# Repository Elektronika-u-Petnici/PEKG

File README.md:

# PEKG - Petnički EKG v2

Petnički EKG snima EKG signal na SD karticu i opcionalno šalje isti pomoću Bluetooth-a i android aplikacije.

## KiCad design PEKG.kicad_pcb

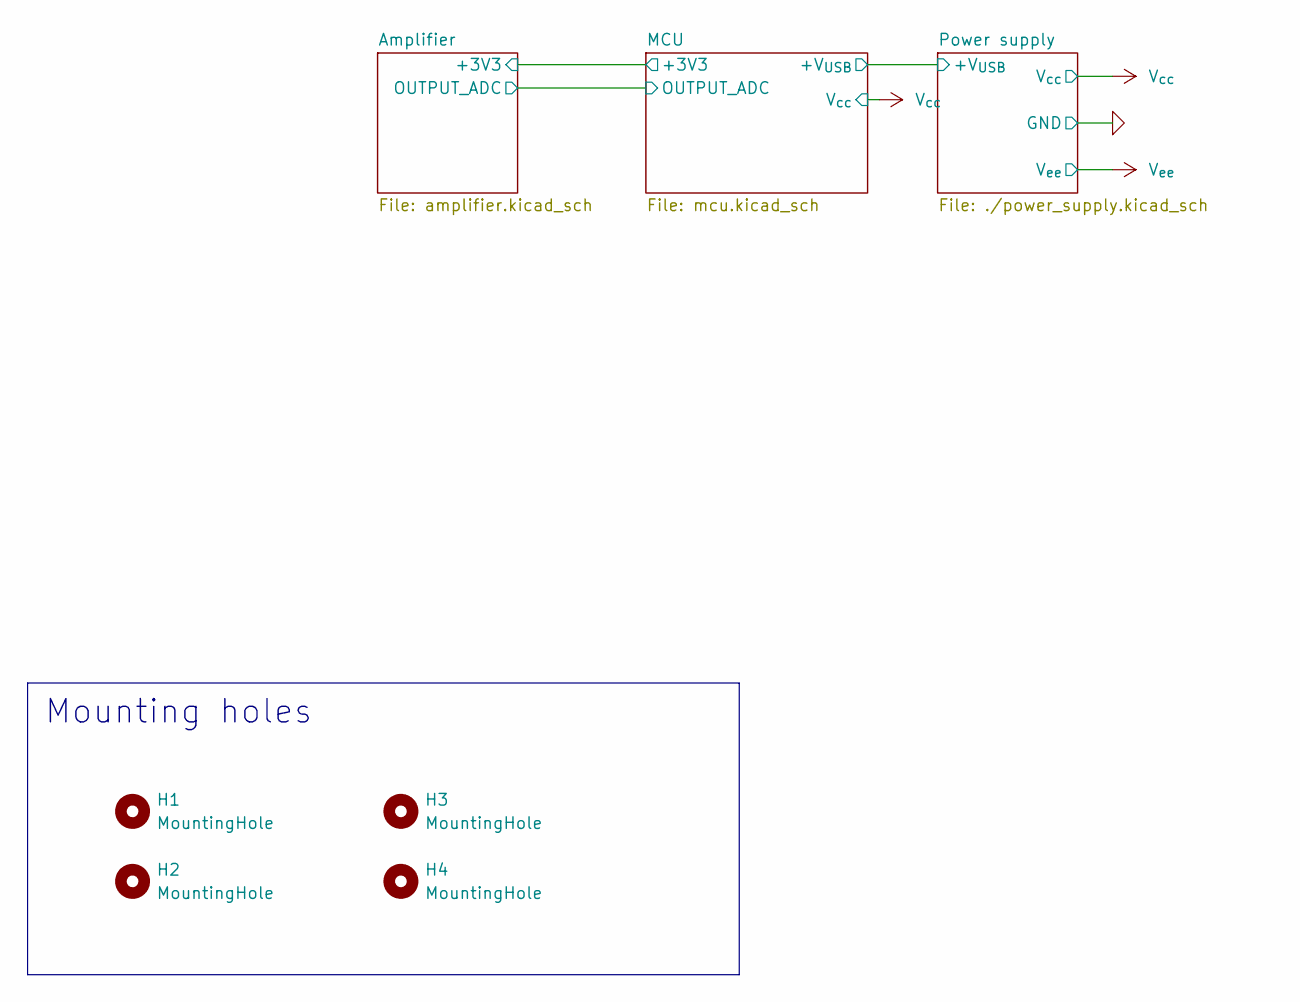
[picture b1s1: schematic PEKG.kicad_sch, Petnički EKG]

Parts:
H1, H3: MountingHole; MountingHole_3.2mm_M3_ISO14580_Pad_TopOnly
H2, H4: MountingHole; MountingHole_3.2mm_M3_ISO14580_Pad_TopBottom

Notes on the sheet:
Mounting holes

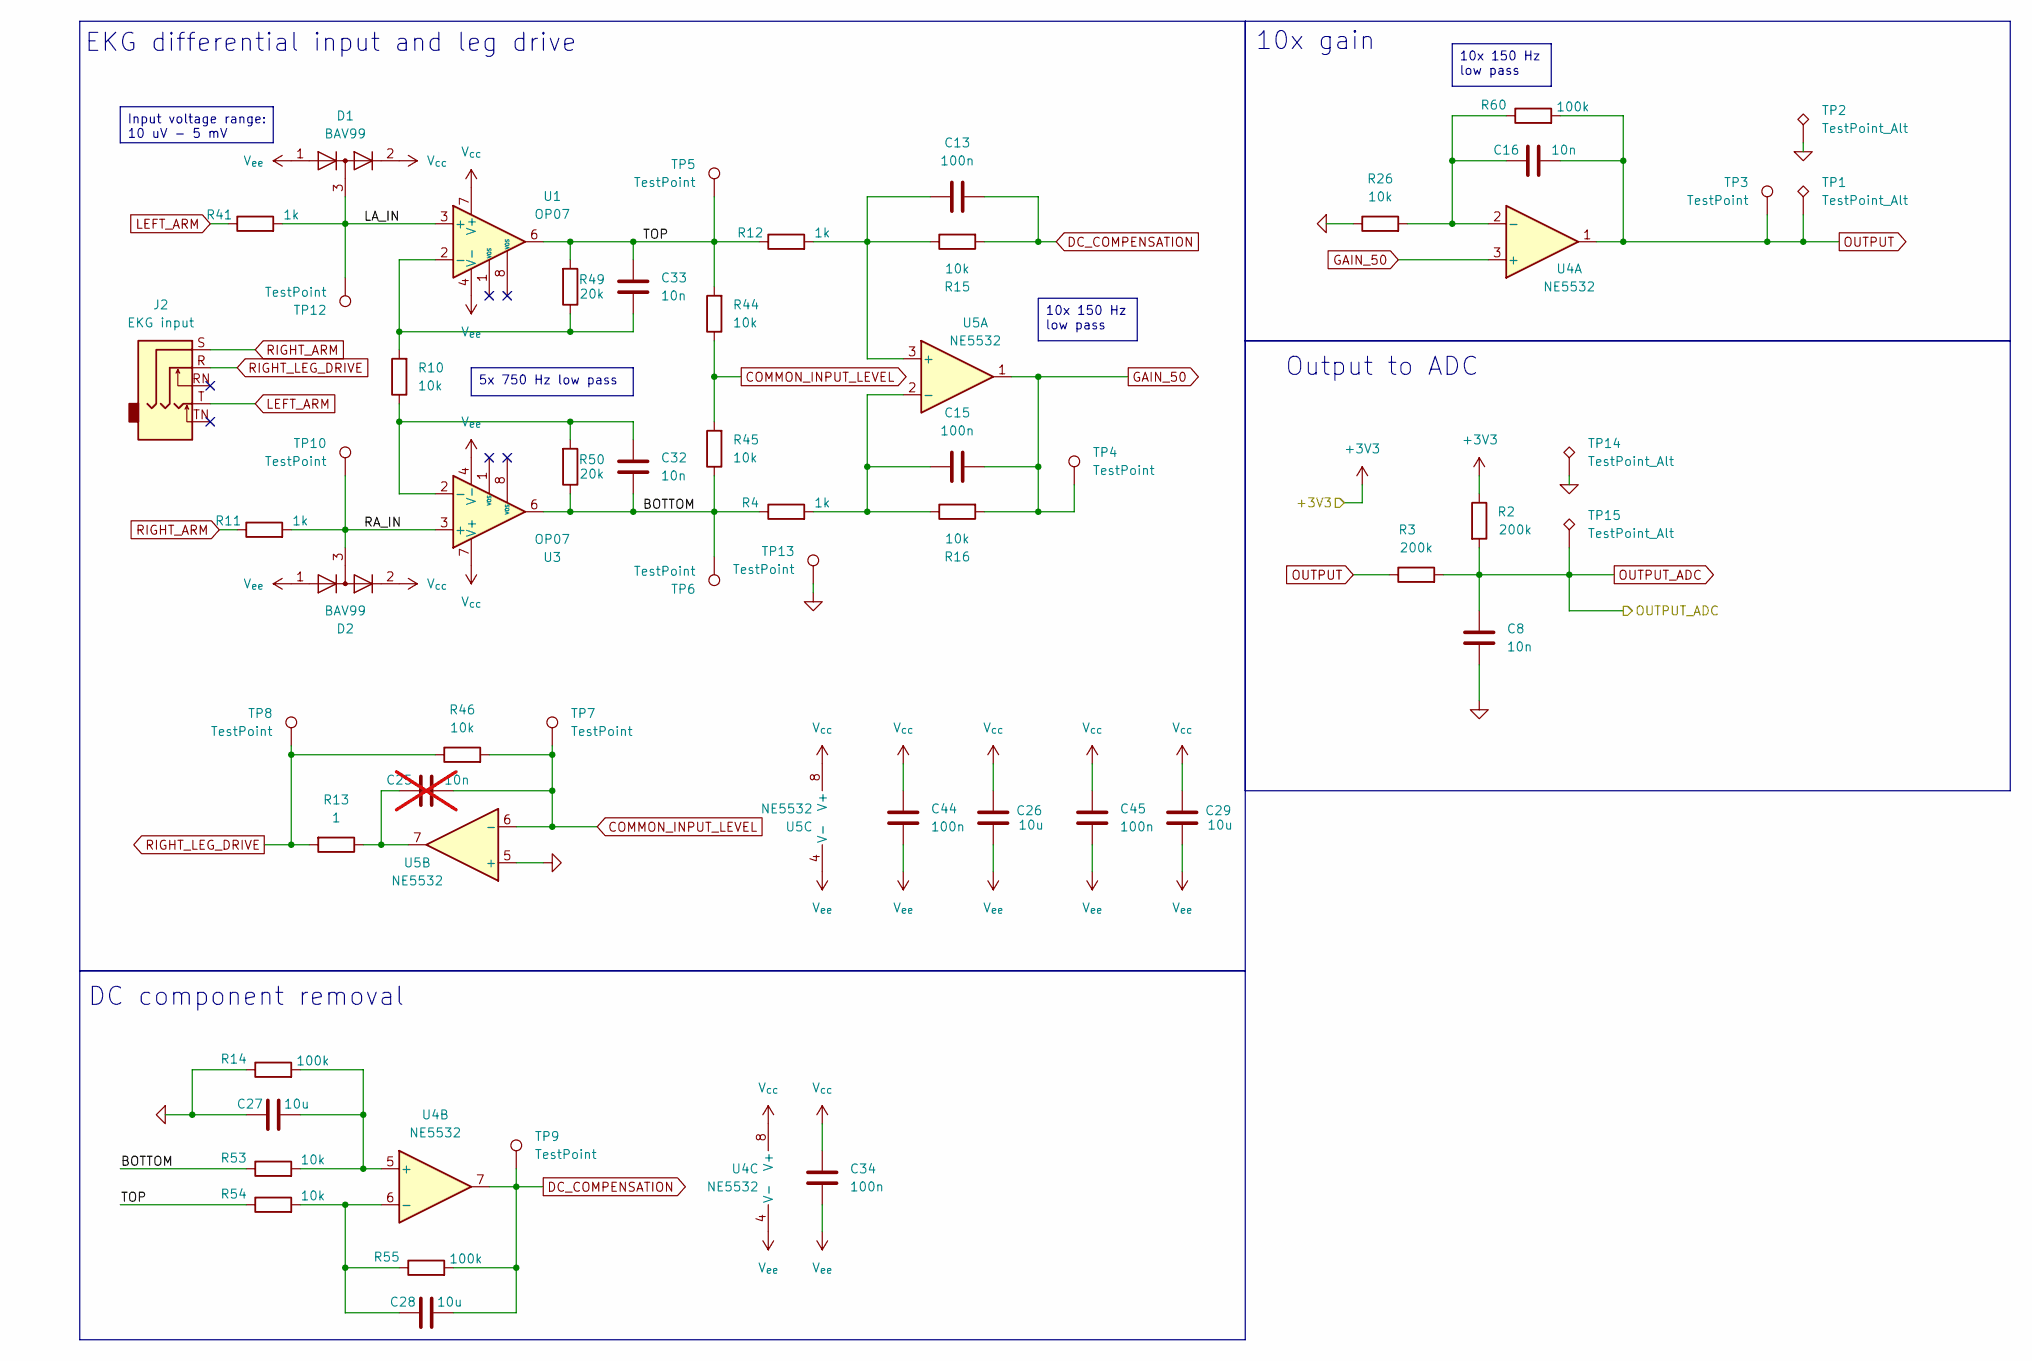
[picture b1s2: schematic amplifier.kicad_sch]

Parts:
C8, C16, C32, C33: 10n; C_0603_1608Metric_Pad1.08x0.95mm_HandSolder; LCSC C57112
C13, C15, C34, C44, C45: 100n; C_0603_1608Metric_Pad1.08x0.95mm_HandSolder; LCSC C14663
C25: 10n; C_0603_1608Metric_Pad1.08x0.95mm_HandSolder; LCSC C57112; not fitted
C26, C27, C28, C29: 10u; C_0603_1608Metric_Pad1.08x0.95mm_HandSolder; LCSC C96446
D1, D2: BAV99; SOT-23; LCSC C2500
J2: EKG input; Jack_3.5mm_CUI_SJ1-3525N_Horizontal
R2, R3: 200k; R_0603_1608Metric_Pad0.98x0.95mm_HandSolder; LCSC C25811
R4, R11, R12, R41: 1k; R_0603_1608Metric_Pad0.98x0.95mm_HandSolder; LCSC C21190
R10, R15, R16, R26, R44, R45, R46, R53, R54: 10k; R_0603_1608Metric_Pad0.98x0.95mm_HandSolder; LCSC C25804
R13: 1; R_0603_1608Metric_Pad0.98x0.95mm_HandSolder; LCSC C22936
R14, R55, R60: 100k; R_0603_1608Metric_Pad0.98x0.95mm_HandSolder; LCSC C25803
R49, R50: 20k; R_0603_1608Metric_Pad0.98x0.95mm_HandSolder; LCSC C4184
TP1, TP2, TP14, TP15: TestPoint_Alt; PinHeader_1x01_P2.54mm_Vertical
TP3, TP4, TP5, TP6, TP7, TP8, TP9, TP10, TP12, TP13: TestPoint; TestPoint_Pad_D3.0mm
U1, U3: OP07; SOIC-8_3.9x4.9mm_P1.27mm; LCSC C7433
U4, U5: NE5532; SOIC-8_3.9x4.9mm_P1.27mm; LCSC C7426

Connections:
0: C8.1, C27.1, R14.1, R26.1, TP2.1 (1_1), TP13.1 (1_1), TP14.1 (1_1), U5.5 (+); also elsewhere on the board
+3V3: R2.1; also elsewhere on the board
/Amplifier/BOTTOM: C32.2, R4.1, R45.1, R50.1, R53.1, TP6.1 (1_1), U3.6
/Amplifier/LA_IN: D1.3 (K), R41.2, TP12.1 (1_1), U1.3 (+)
/Amplifier/RA_IN: D2.3 (K), R11.2, TP10.1 (1_1), U3.3 (+)
/Amplifier/TOP: C33.1, R12.1, R44.2, R49.2, R54.1, TP5.1 (1_1), U1.6
COMMON_INPUT_LEVEL: C25.1, R44.1, R45.2, R46.2, TP7.1 (1_1), U5.6 (-)
DC_COMPENSATION: C13.1, C28.2, R15.2, R55.2, TP9.1 (1_1), U4.7
GAIN_50: C15.1, R16.2, TP4.1 (1_1), U4.3 (+), U5.1
LEFT_ARM: J2.T, R41.1
unnamed: C25.2, R13.1, U5.7
unnamed: C33.2, R10.2, R49.1, U1.2 (-)
unnamed: C32.1, R10.1, R50.2, U3.2 (-)
unnamed: C16.2, R26.2, R60.1, U4.2 (-)
unnamed: C27.2, R14.2, R53.2, U4.5 (+)
unnamed: C28.1, R54.2, R55.1, U4.6 (-)
unnamed: C13.2, R12.2, R15.1, U5.3 (+)
unnamed: C15.2, R4.2, R16.1, U5.2 (-)
OUTPUT: C16.1, R3.1, R60.2, TP1.1 (1_1), TP3.1 (1_1), U4.1; also elsewhere on the board
OUTPUT_ADC: C8.2, R2.2, R3.2, TP15.1 (1_1); also elsewhere on the board
RIGHT_ARM: J2.S, R11.1
RIGHT_LEG_DRIVE: J2.R, R13.2, R46.1, TP8.1 (1_1)
V_{cc}: C26.1, C29.1, C34.2, C44.2, C45.2, D1.2 (A), D2.2 (A), U1.7 (V+), U3.7 (V+), U4.8 (V+), U5.8 (V+); also elsewhere on the board
V_{ee}: C26.2, C29.2, C34.1, C44.1, C45.1, D1.1 (K), D2.1 (K), U1.4 (V-), U3.4 (V-), U4.4 (V-), U5.4 (V-); also elsewhere on the board

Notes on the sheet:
EKG differential input and leg drive
Output to ADC
10x gain
DC component removal
Input voltage range: 10 uV - 5 mV
5x 750 Hz low pass
10x 150 Hz low pass

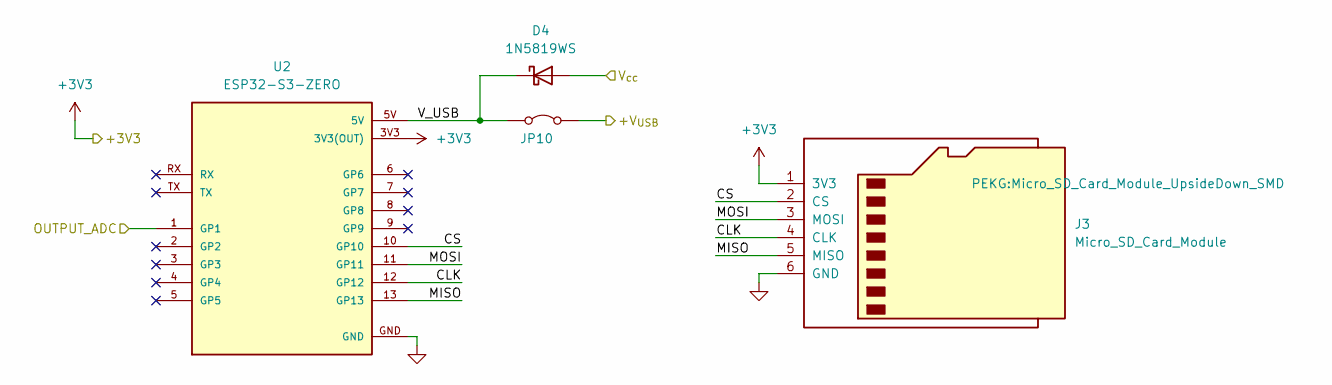
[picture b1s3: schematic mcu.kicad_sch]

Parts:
D4: 1N5819WS; D_SOD-323; LCSC C191023
J3: Micro_SD_Card_Module; Micro_SD_Card_Module_UpsideDown_SMD
JP10: Jumper_2_Bridged; SolderJumper-2_P1.3mm_Bridged_RoundedPad1.0x1.5mm
U2: ESP32-S3-ZERO; MODULE_ESP32-S3-ZERO_SMD; PARTREV NA

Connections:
0: J3.6 (GND), U2.GND; also elsewhere on the board
+3V3: J3.1 (3V3), U2.3V3 (3V3(OUT)); also elsewhere on the board
+V_{USB}: JP10.2 (B); also elsewhere on the board
/MCU/CLK: J3.4 (CLK), U2.12 (GP12)
/MCU/CS: J3.2 (CS), U2.10 (GP10)
/MCU/MISO: J3.5 (MISO), U2.13 (GP13)
/MCU/MOSI: J3.3 (MOSI), U2.11 (GP11)
/MCU/V_USB: D4.1 (K), JP10.1 (A), U2.5V
OUTPUT_ADC: U2.1 (GP1); also elsewhere on the board
V_{cc}: D4.2 (A); also elsewhere on the board

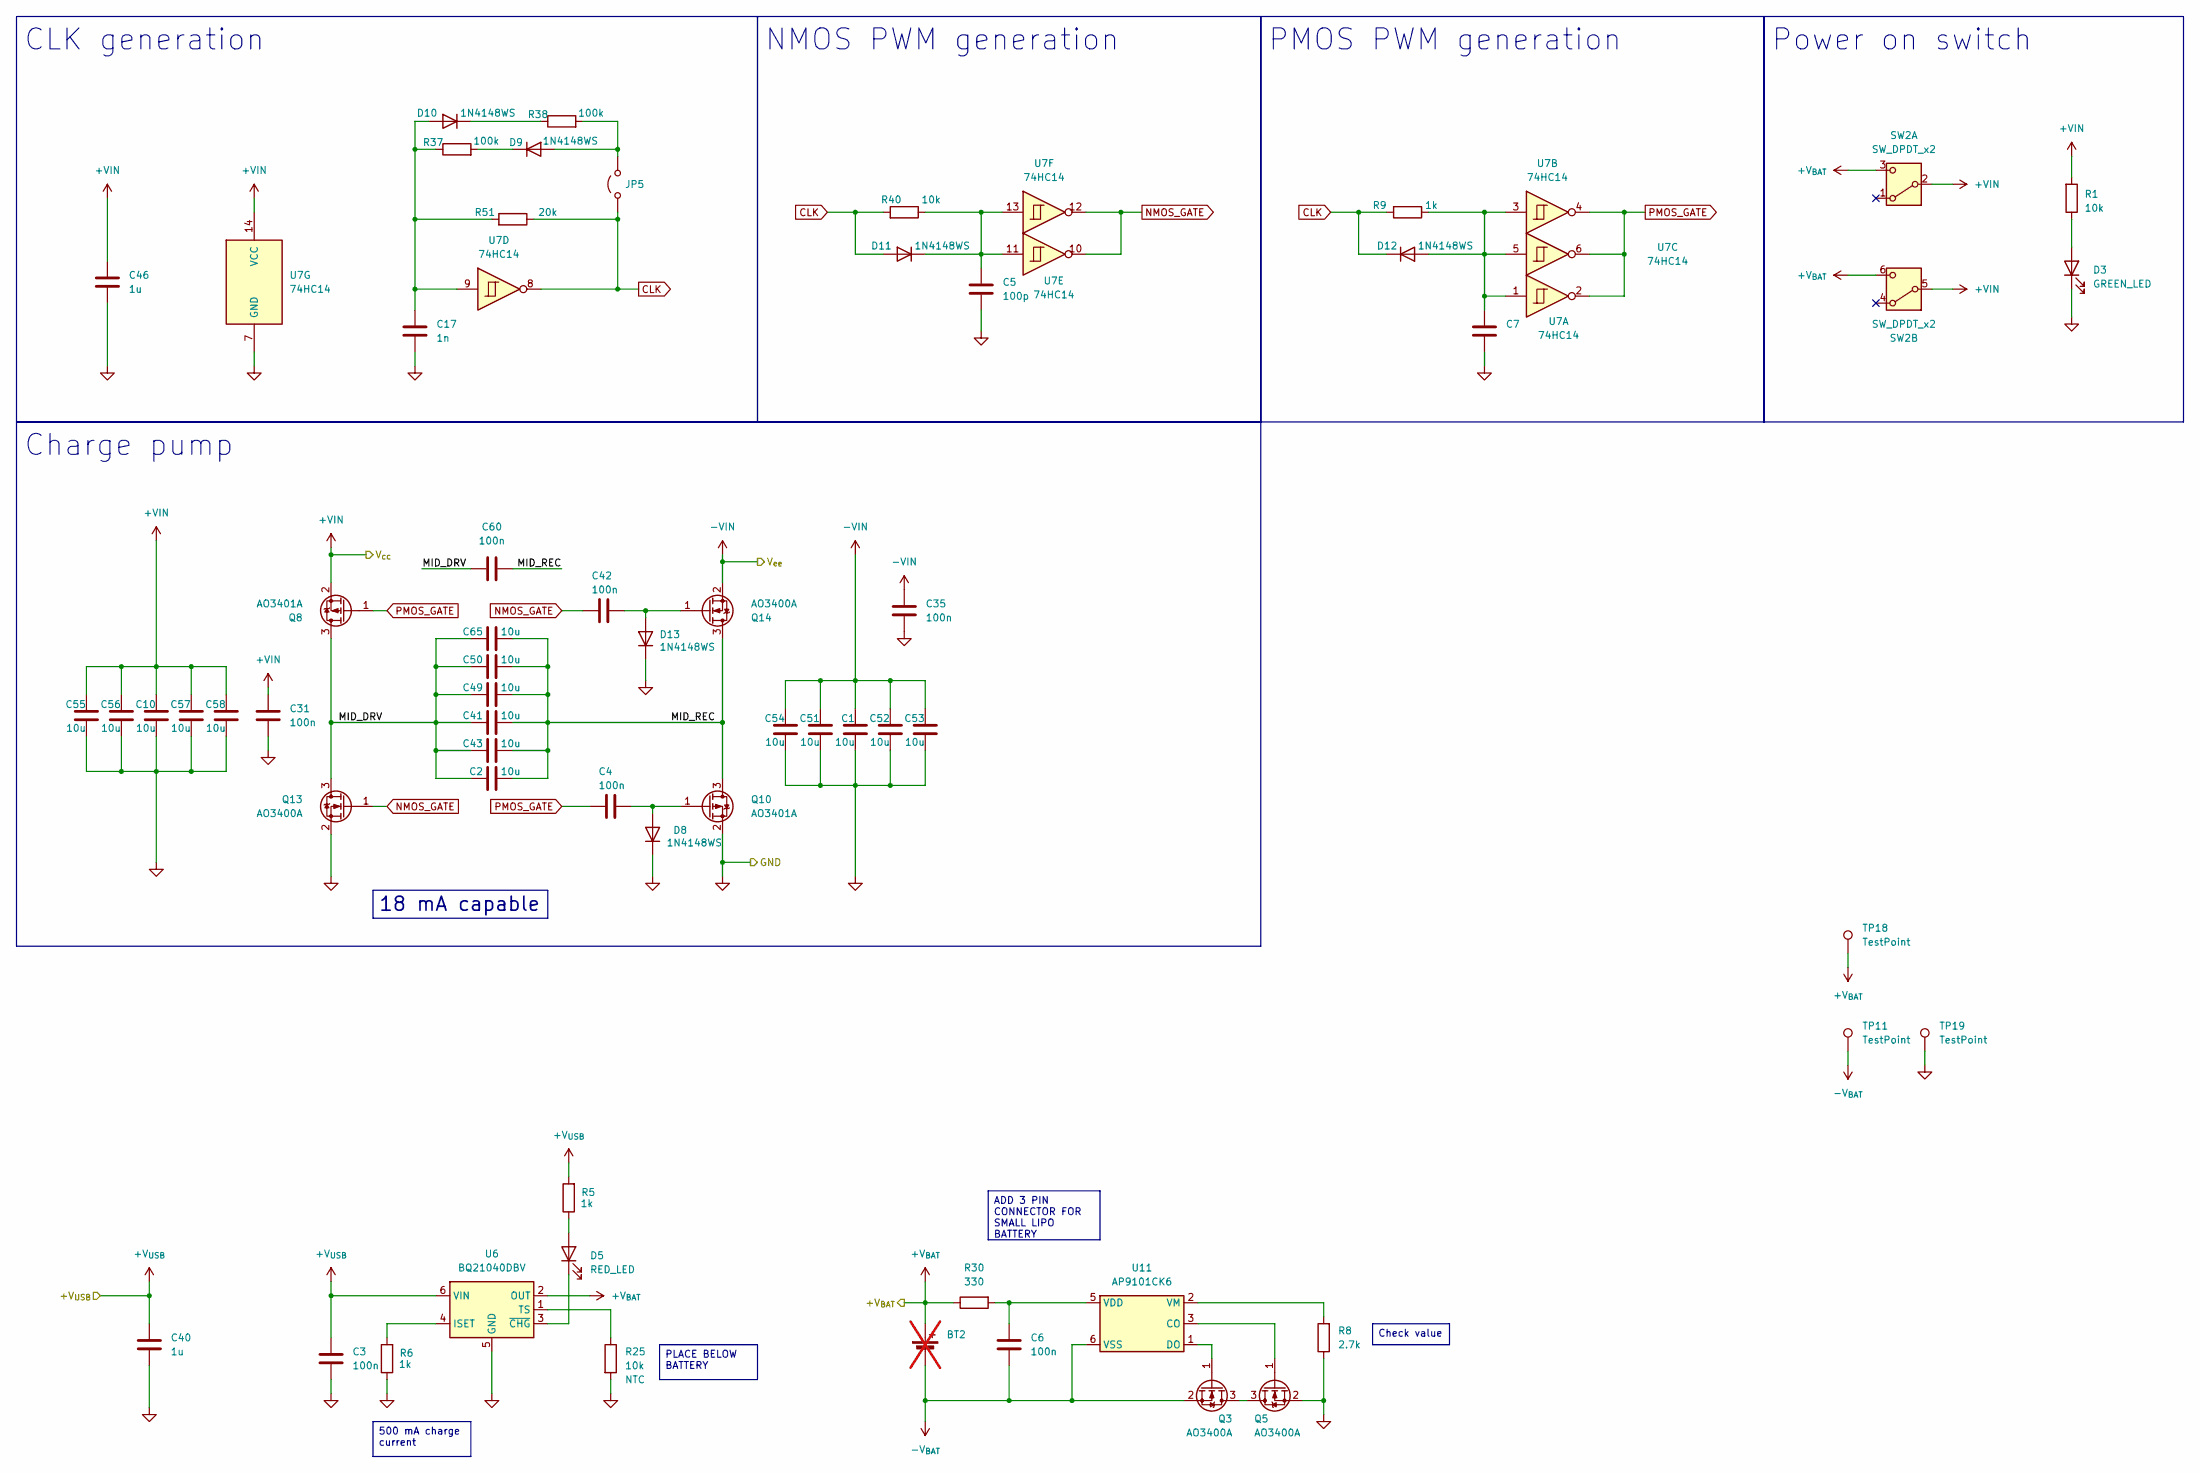
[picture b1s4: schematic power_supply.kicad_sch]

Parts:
BT2: Battery_Cell; battery_holder; not fitted
C1, C2, C10, C41, C43, C49, C50, C51, C52, C53, C54, C55, C56, C57, C58, C65: 10u; R_0805_2012Metric_Pad1.20x1.40mm_HandSolder; Voltage 25V; LCSC C15850
C3, C4, C6, C31, C35, C42, C60: 100n; C_0603_1608Metric_Pad1.08x0.95mm_HandSolder; LCSC C14663
C5, C7: 100p; C_0603_1608Metric_Pad1.08x0.95mm_HandSolder; LCSC C14858
C17: 1n; C_0603_1608Metric_Pad1.08x0.95mm_HandSolder; LCSC C1588
C40, C46: 1u; C_0603_1608Metric_Pad1.08x0.95mm_HandSolder; LCSC C15849
D3: GREEN_LED; LED_0805_2012Metric_Pad1.15x1.40mm_HandSolder; LCSC C2297
D5: RED_LED; LED_0805_2012Metric_Pad1.15x1.40mm_HandSolder; LCSC C84256
D8, D9, D10, D11, D12, D13: 1N4148WS; D_SOD-323; LCSC C2128
JP5: Jumper_2_Open; SolderJumper-2_P1.3mm_Open_RoundedPad1.0x1.5mm
Q3, Q5, Q13, Q14: AO3400A; SOT-23; LCSC C20917
Q8, Q10: AO3401A; SOT-23; LCSC C15127
R1, R25, R40: 10k; R_0603_1608Metric_Pad0.98x0.95mm_HandSolder; LCSC C25804
R5, R6, R9: 1k; R_0603_1608Metric_Pad0.98x0.95mm_HandSolder; LCSC C21190
R8: 2.7k; R_0603_1608Metric_Pad0.98x0.95mm_HandSolder; LCSC C13167
R30: 330; R_0603_1608Metric_Pad0.98x0.95mm_HandSolder; LCSC C23138
R37, R38: 100k; R_0603_1608Metric_Pad0.98x0.95mm_HandSolder; LCSC C25803
R51: 20k; R_0603_1608Metric_Pad0.98x0.95mm_HandSolder; LCSC C4184
SW2: SW_DPDT_x2; SW_EG1271
TP11, TP18, TP19: TestPoint; TestPoint_Pad_D3.0mm
U6: BQ21040DBV; SOT-23-6
U7: 74HC14; SOIC-14_3.9x8.7mm_P1.27mm
U11: AP9101CK6; SOT-23-6_Handsoldering

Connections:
0: C1.1, C3.1, C5.1, C7.1, C10.1, C17.1, C31.1, C35.1, C40.1, C46.1, C51.1, C52.1, C53.1, C54.1, C55.1, C56.1, C57.1, C58.1, D3.1 (K), D8.1 (K), D13.1 (K), Q5.2 (S), Q10.2 (S), Q13.2 (S), R6.1, R8.1, R25.2, TP19.1 (1_1), U6.5 (GND), U7.7 (GND); also elsewhere on the board
+V_{BAT}: BT2.1 (+), R30.1, SW2.3 (C), SW2.6 (C), TP18.1 (1_1), U6.2 (OUT)
+V_{USB}: C3.2, C40.2, R5.2, U6.6 (VIN); also elsewhere on the board
-V_{BAT}: BT2.2 (-), C6.1, Q3.2 (S), TP11.1 (1_1), U11.6 (VSS)
/Power supply/MID_DRV: C2.1, C41.1, C43.1, C49.1, C50.1, C60.2, C65.1, Q8.3 (D), Q13.3 (D)
/Power supply/MID_REC: C2.2, C41.2, C43.2, C49.2, C50.2, C60.1, C65.2, Q10.3 (D), Q14.3 (D)
CLK: D11.2 (A), D12.1 (K), JP5.1 (A), R9.2, R40.2, R51.1, U7.8
NMOS_GATE: C42.1, Q13.1 (G), U7.10, U7.12
unnamed: D3.2 (A), R1.1
unnamed: D5.2 (A), R5.1
unnamed: D5.1 (K), U6.3 (~CHG)
unnamed: C4.2, D8.2 (A), Q10.1 (G)
unnamed: D9.2 (A), JP5.2 (B), R38.2
unnamed: D9.1 (K), R37.2
unnamed: C17.2, D10.2 (A), R37.1, R51.2, U7.9
unnamed: D10.1 (K), R38.1
unnamed: C5.2, D11.1 (K), R40.1, U7.11, U7.13
unnamed: C7.2, D12.2 (A), R9.1, U7.1, U7.3, U7.5
unnamed: C42.2, D13.2 (A), Q14.1 (G)
unnamed: Q3.3 (D), Q5.3 (D)
unnamed: Q3.1 (G), U11.1 (DO)
unnamed: Q5.1 (G), U11.3 (CO)
unnamed: R6.2, U6.4 (ISET)
unnamed: R25.1, U6.1 (TS)
unnamed: C6.2, R30.2, U11.5 (VDD)
unnamed: R8.2, U11.2 (VM)
PMOS_GATE: C4.1, Q8.1 (G), U7.2, U7.4, U7.6
V_{cc}: C10.2, C31.2, C46.2, C55.2, C56.2, C57.2, C58.2, Q8.2 (S), R1.2, SW2.2 (B), SW2.5 (B), U7.14 (VCC); also elsewhere on the board
V_{ee}: C1.2, C35.2, C51.2, C52.2, C53.2, C54.2, Q14.2 (S); also elsewhere on the board

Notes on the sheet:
Power on switch
Charge pump
CLK generation
NMOS PWM generation
PMOS PWM generation
Check value
ADD 3 PIN CONNECTOR FOR SMALL LIPO BATTERY
PLACE BELOW BATTERY
500 mA charge current
18 mA capable

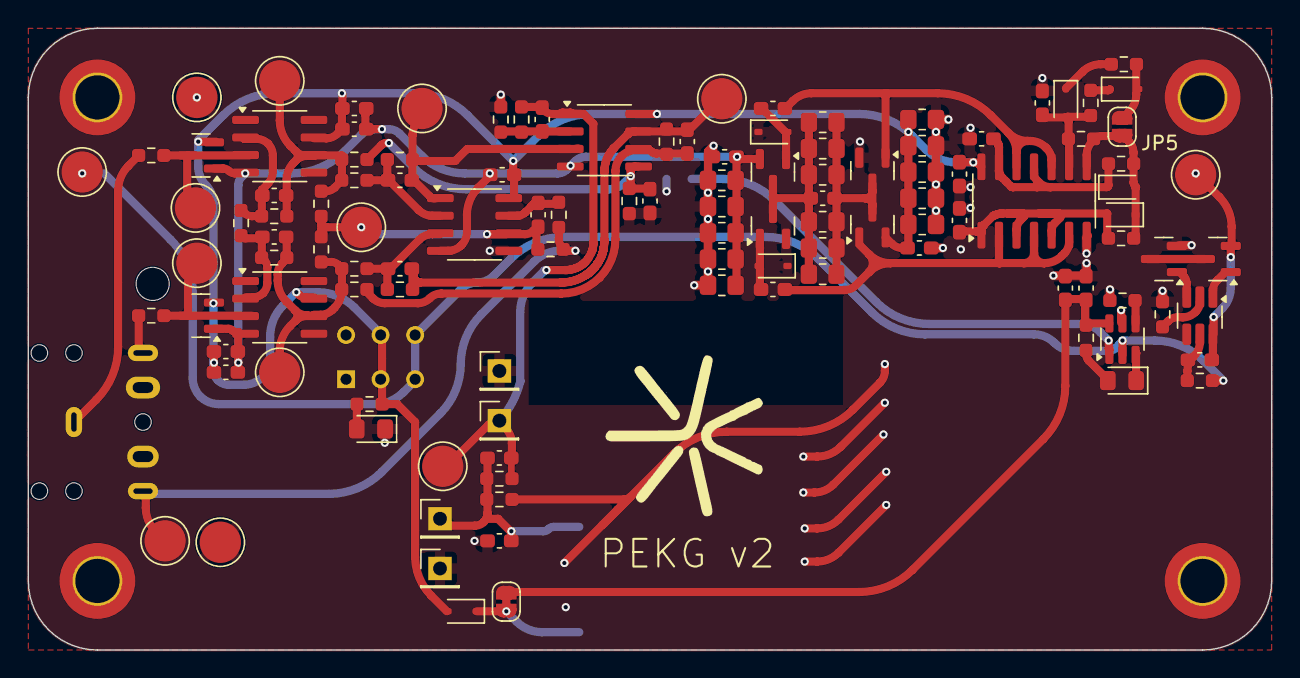
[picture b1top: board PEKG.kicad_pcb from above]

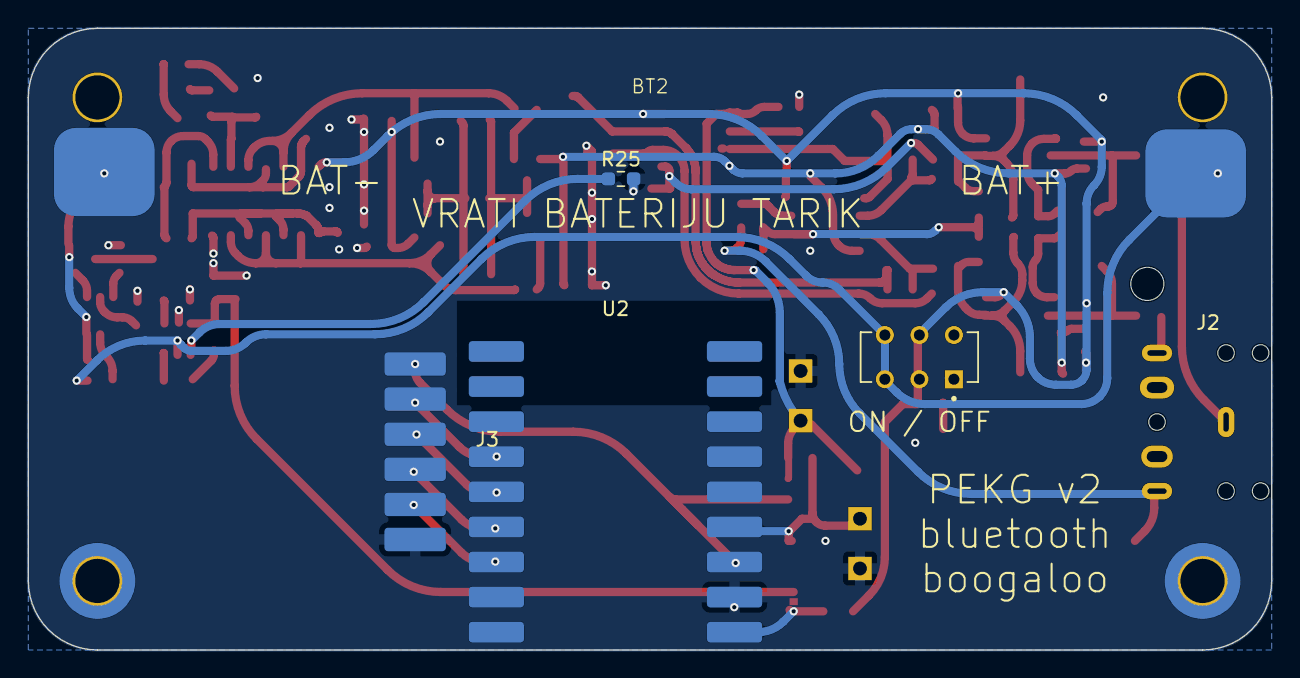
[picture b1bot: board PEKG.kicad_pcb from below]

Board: 2 copper layers, 90.0 x 45.0 mm, 127 parts (6 on the bottom side), 55 nets.

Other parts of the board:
C9: 10u; C_0603_1608Metric_Pad1.08x0.95mm_HandSolder

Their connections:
OUTPUT: C9.1; also elsewhere on the board
OUTPUT_ADC: C9.2; also elsewhere on the board
